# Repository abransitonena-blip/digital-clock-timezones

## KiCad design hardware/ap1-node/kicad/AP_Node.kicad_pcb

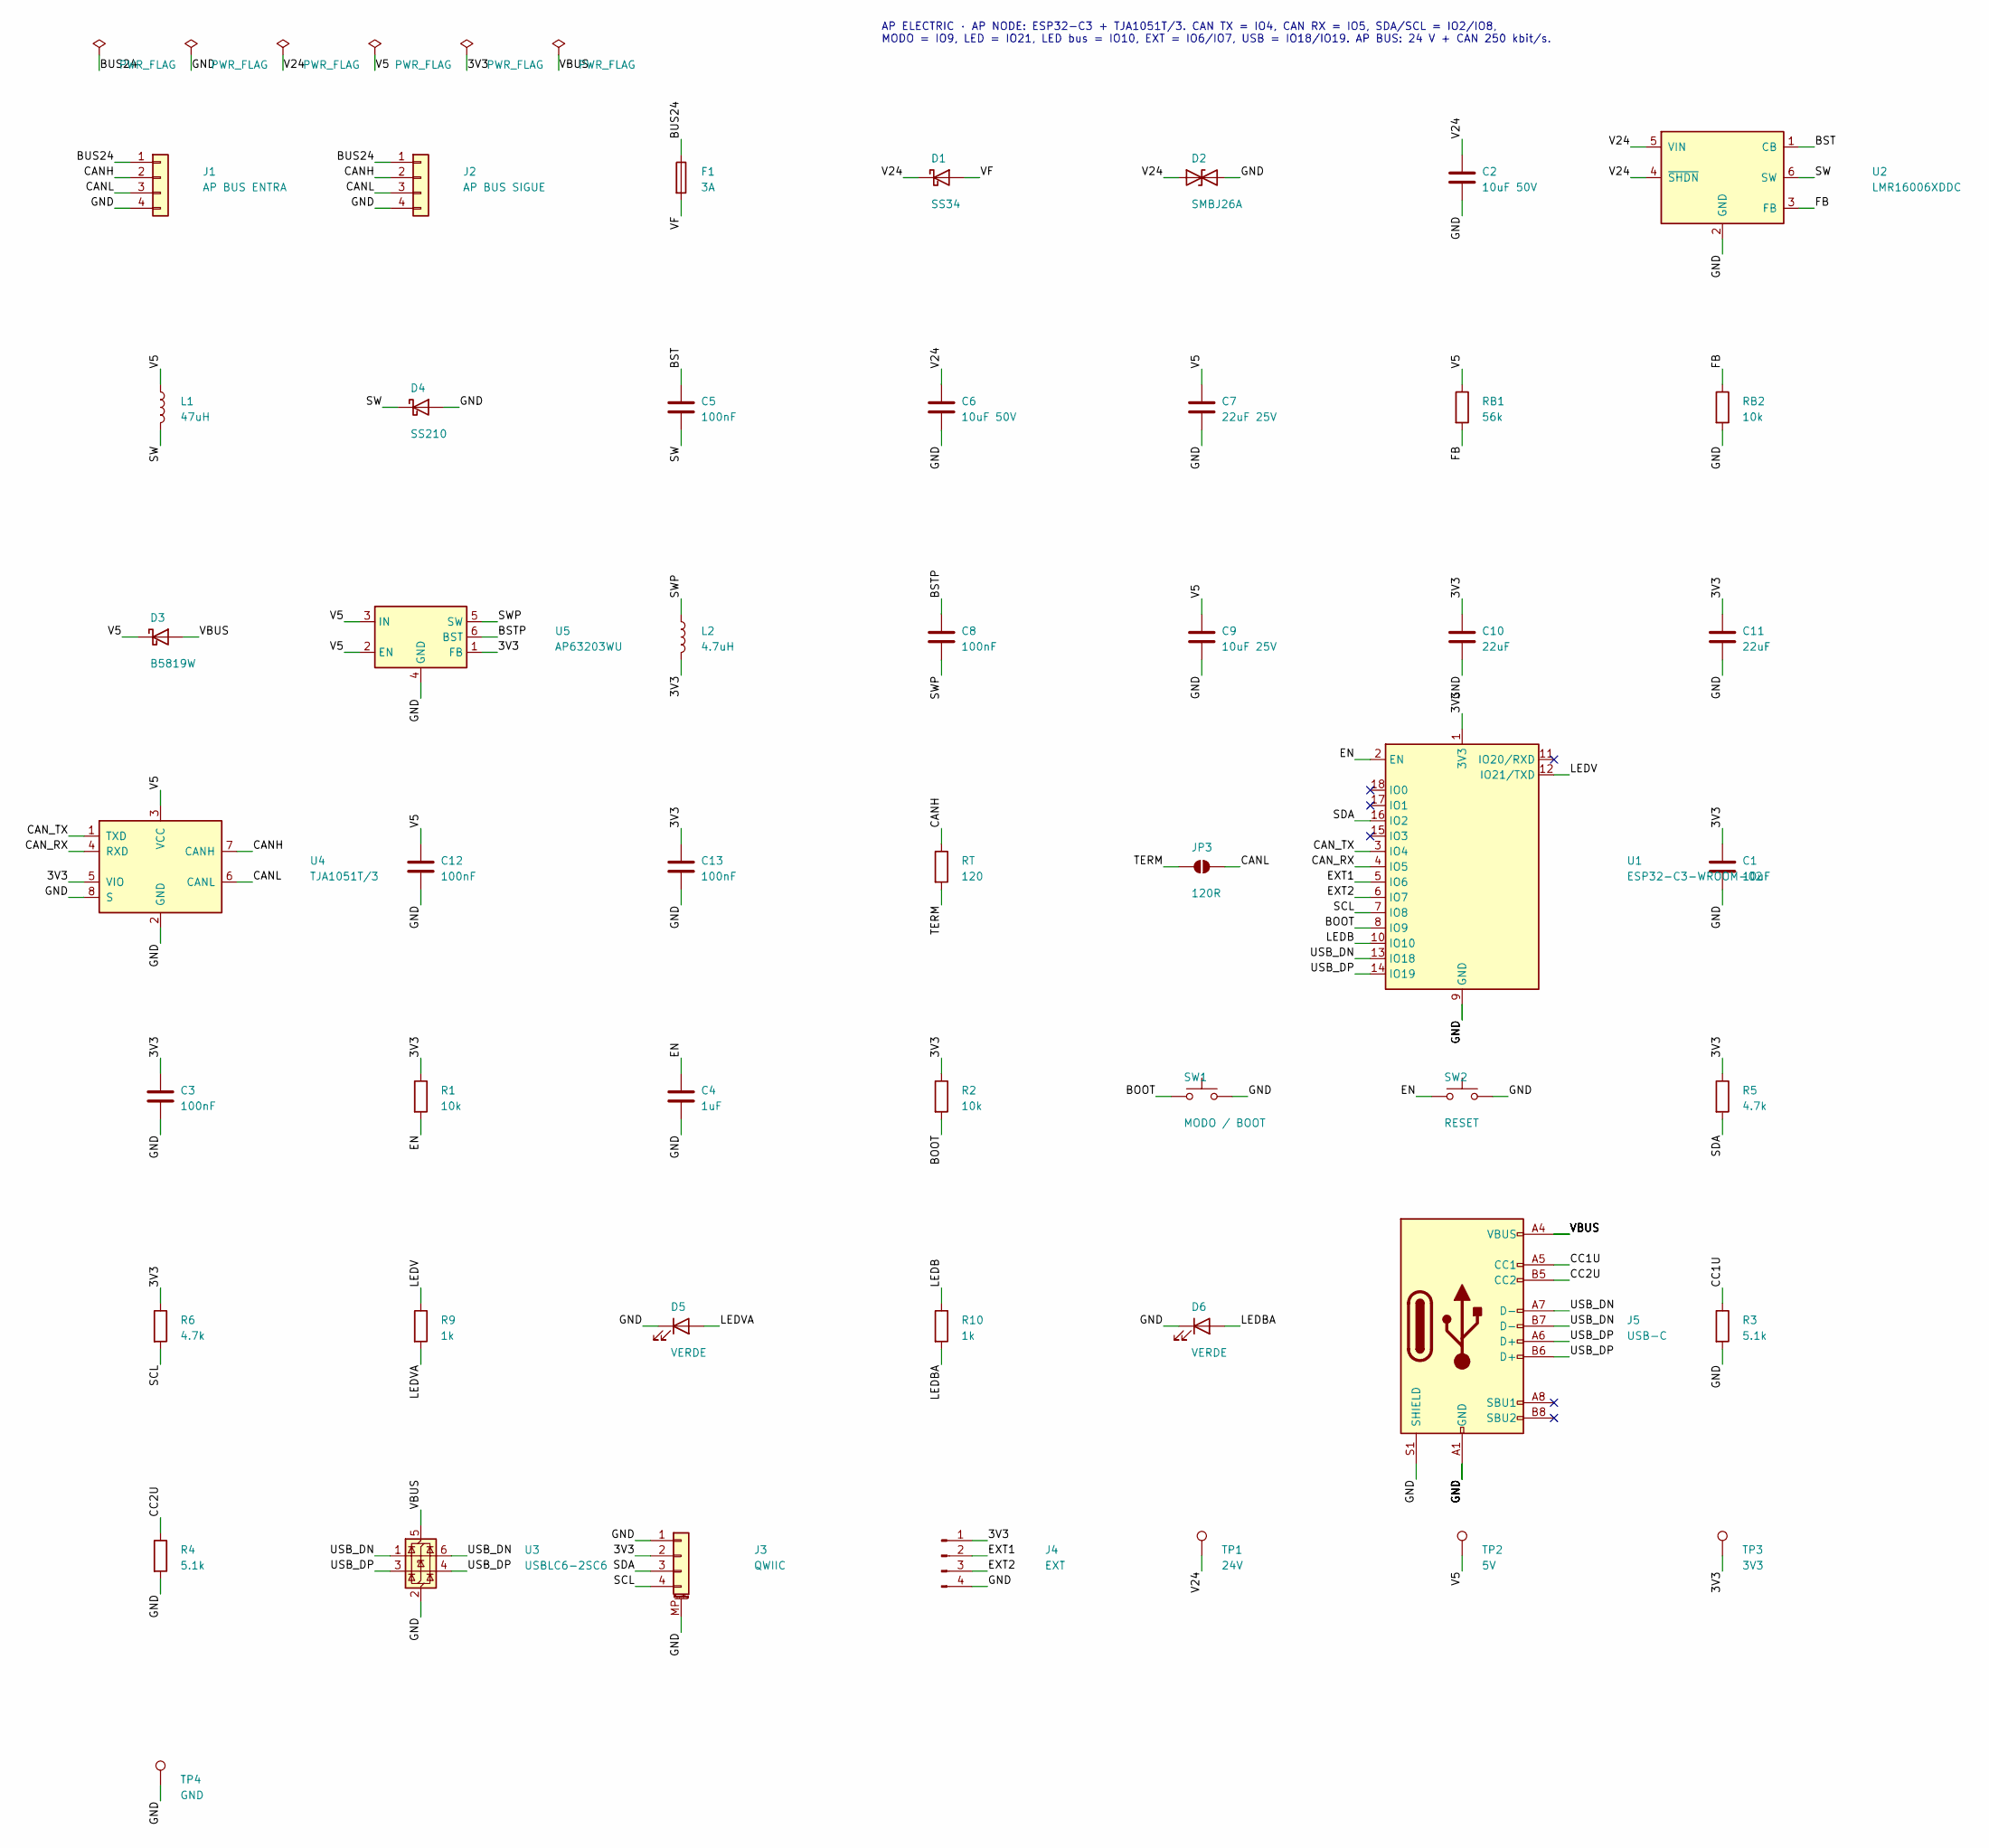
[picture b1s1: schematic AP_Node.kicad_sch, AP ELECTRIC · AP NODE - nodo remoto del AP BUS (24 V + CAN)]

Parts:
C1: 10uF; C_0805_2012Metric
C2, C6: 10uF 50V; C_1206_3216Metric
C3, C5, C8, C12, C13: 100nF; C_0603_1608Metric
C4: 1uF; C_0603_1608Metric
C7: 22uF 25V; C_1206_3216Metric
C9: 10uF 25V; C_1206_3216Metric
C10, C11: 22uF; C_0805_2012Metric
D1: SS34; D_SMA
D2: SMBJ26A; D_SMB
D3: B5819W; D_SOD-123
D4: SS210; D_SMA
D5, D6: VERDE; LED_0603_1608Metric
F1: 3A; Fuse_1206_3216Metric
J1: AP BUS ENTRA; JST_XH_B4B-XH-A_1x04_P2.50mm_Vertical
J2: AP BUS SIGUE; JST_XH_B4B-XH-A_1x04_P2.50mm_Vertical
J3: QWIIC; JST_SH_SM04B-SRSS-TB_1x04-1MP_P1.00mm_Horizontal
J4: EXT; PinHeader_1x04_P2.54mm_Vertical
J5: USB-C; USB_C_Receptacle_HRO_TYPE-C-31-M-12
JP3: 120R; SolderJumper-2_P1.3mm_Open_RoundedPad1.0x1.5mm
L1: 47uH; L_Changjiang_FNR4030S
L2: 4.7uH; L_Changjiang_FNR4030S
R1, R2: 10k; R_0603_1608Metric
R3, R4: 5.1k; R_0603_1608Metric
R5, R6: 4.7k; R_0603_1608Metric
R9, R10: 1k; R_0603_1608Metric
RB1: 56k; R_0603_1608Metric
RB2: 10k; R_0603_1608Metric
RT: 120; R_1206_3216Metric
SW1: MODO / BOOT; SW_Push_1P1T_XKB_TS-1187A
SW2: RESET; SW_Push_1P1T_XKB_TS-1187A
TP1: 24V; TestPoint_Pad_D1.5mm
TP2: 5V; TestPoint_Pad_D1.5mm
TP3: 3V3; TestPoint_Pad_D1.5mm
TP4: GND; TestPoint_Pad_D1.5mm
U1: ESP32-C3-WROOM-02; ESP32-C3-WROOM-02_JLC
U2: LMR16006XDDC; SOT-23-6
U3: USBLC6-2SC6; SOT-23-6
U4: TJA1051T/3; SOIC-8_3.9x4.9mm_P1.27mm
U5: AP63203WU; TSOT-23-6

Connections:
/3V3: C1.1, C3.1, C10.1, C11.1, C13.1, J3.2, J4.1, L2.2, R1.1, R2.1, R5.1, R6.1, TP3.1, U1.1 (3V3), U4.5 (VIO), U5.1 (FB)
/BOOT: R2.2, SW1.1, U1.8 (IO9)
/BST: C5.1, U2.1 (CB)
/BSTP: C8.1, U5.6 (BST)
/BUS24: F1.1, J1.1, J2.1
/CANH: J1.2, J2.2, RT.1, U4.7 (CANH)
/CANL: J1.3, J2.3, JP3.2 (B), U4.6 (CANL)
/CAN_RX: U1.4 (IO5), U4.4 (RXD)
/CAN_TX: U1.3 (IO4), U4.1 (TXD)
/CC1U: J5.A5 (CC1), R3.1
/CC2U: J5.B5 (CC2), R4.1
/EN: C4.1, R1.2, SW2.1, U1.2 (EN)
/EXT1: J4.2, U1.5 (IO6)
/EXT2: J4.3, U1.6 (IO7)
/FB: RB1.2, RB2.1, U2.3 (FB)
/GND: C1.2, C2.2, C3.2, C4.2, C6.2, C7.2, C9.2, C10.2, C11.2, C12.2, C13.2, D2.2 (A2), D4.2 (A), D5.1 (K), D6.1 (K), J1.4, J2.4, J3.1, J3.MP (MountPin), J4.4, J5.A1 (GND), J5.A12 (GND), J5.B1 (GND), J5.B12 (GND), J5.S1 (SHIELD), R3.2, R4.2, RB2.2, SW1.2, SW2.2, TP4.1, U1.9 (GND), U1.19 (GND), U2.2 (GND), U3.2 (GND), U4.2 (GND), U4.8 (S), U5.4 (GND)
/LEDB: R10.1, U1.10 (IO10)
/LEDBA: D6.2 (A), R10.2
/LEDV: R9.1, U1.12 (IO21/TXD)
/LEDVA: D5.2 (A), R9.2
/SCL: J3.4, R6.2, U1.7 (IO8)
/SDA: J3.3, R5.2, U1.16 (IO2)
/SW: C5.2, D4.1 (K), L1.2, U2.6 (SW)
/SWP: C8.2, L2.1, U5.5 (SW)
/TERM: JP3.1 (A), RT.2
/USB_DN: J5.A7 (D-), J5.B7 (D-), U1.13 (IO18), U3.1 (I/O1), U3.6 (I/O1)
/USB_DP: J5.A6 (D+), J5.B6 (D+), U1.14 (IO19), U3.3 (I/O2), U3.4 (I/O2)
/V5: C7.1, C9.1, C12.1, D3.1 (K), L1.1, RB1.1, TP2.1, U4.3 (VCC), U5.2 (EN), U5.3 (IN)
/V24: C2.1, C6.1, D1.1 (K), D2.1 (A1), TP1.1, U2.4 (~SHDN), U2.5 (VIN)
/VBUS: D3.2 (A), J5.A4 (VBUS), J5.A9 (VBUS), J5.B4 (VBUS), J5.B9 (VBUS), U3.5 (VBUS)
/VF: D1.2 (A), F1.2

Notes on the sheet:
AP ELECTRIC · AP NODE: ESP32-C3 + TJA1051T/3. CAN TX = IO4, CAN RX = IO5, SDA/SCL = IO2/IO8, MODO = IO9, LED = IO21, LED bus = IO10, EXT = IO6/IO7, USB = IO18/IO19. AP BUS: 24 V + CAN 250 kbit/s.

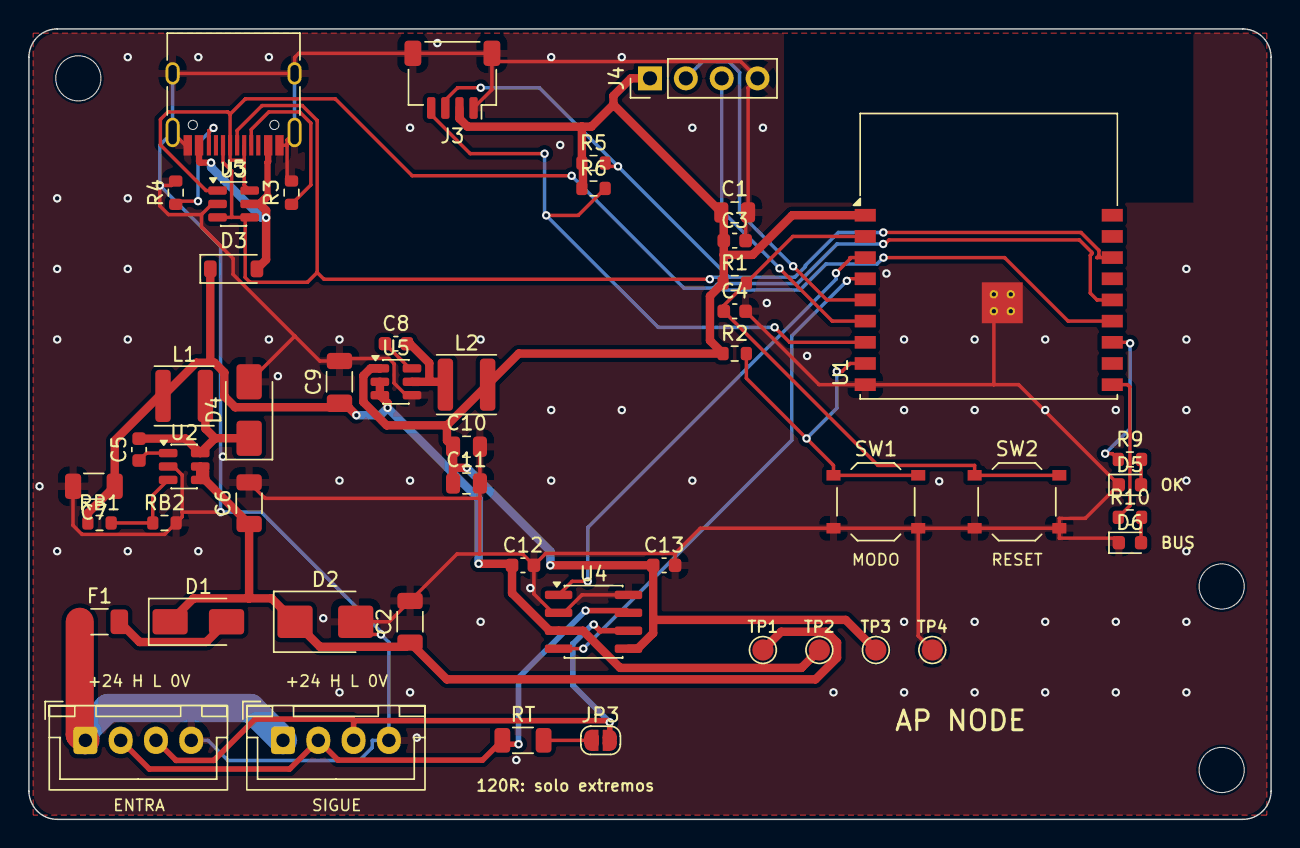
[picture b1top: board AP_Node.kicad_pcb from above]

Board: 2 copper layers, 88.0 x 56.0 mm, 53 parts (0 on the bottom side), 31 nets.

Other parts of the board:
H1, H2, H3: MountingHole_3.2mm_M3

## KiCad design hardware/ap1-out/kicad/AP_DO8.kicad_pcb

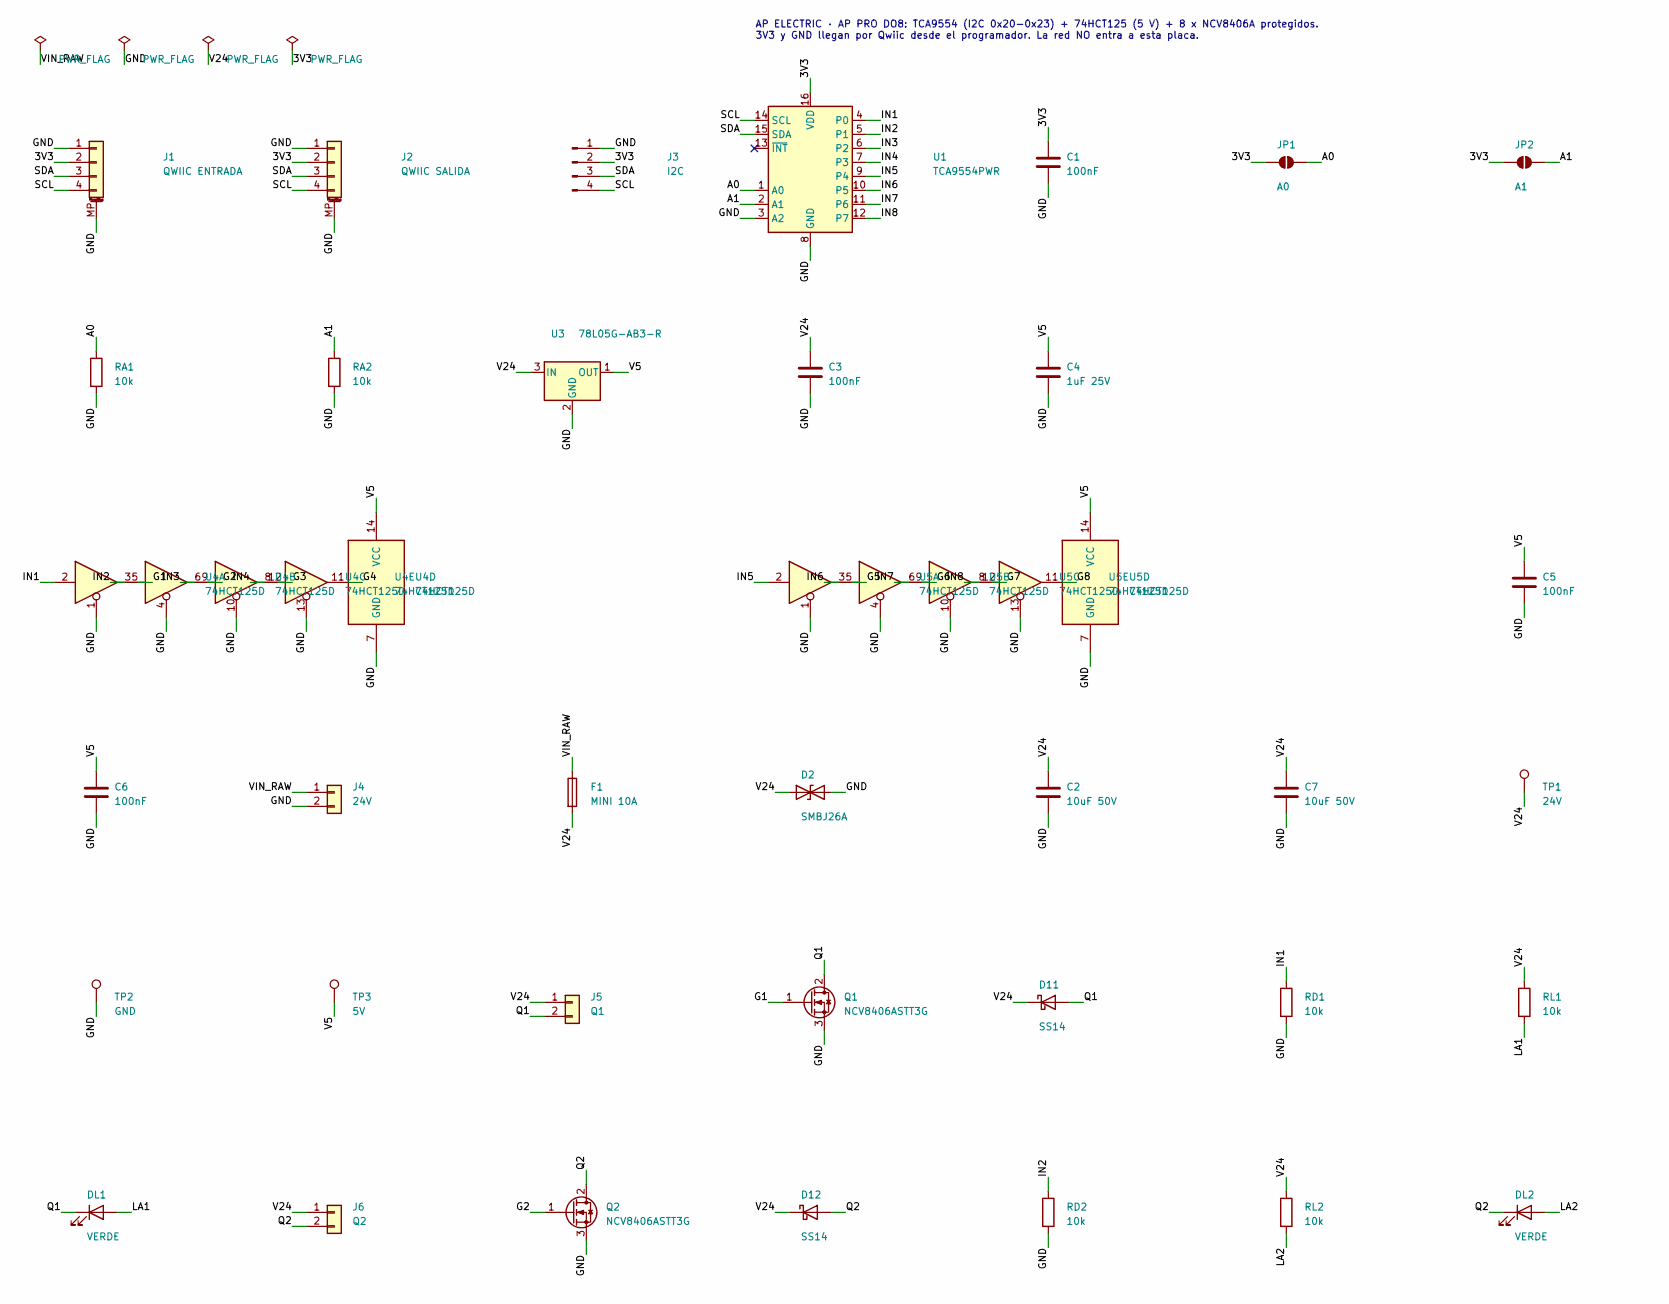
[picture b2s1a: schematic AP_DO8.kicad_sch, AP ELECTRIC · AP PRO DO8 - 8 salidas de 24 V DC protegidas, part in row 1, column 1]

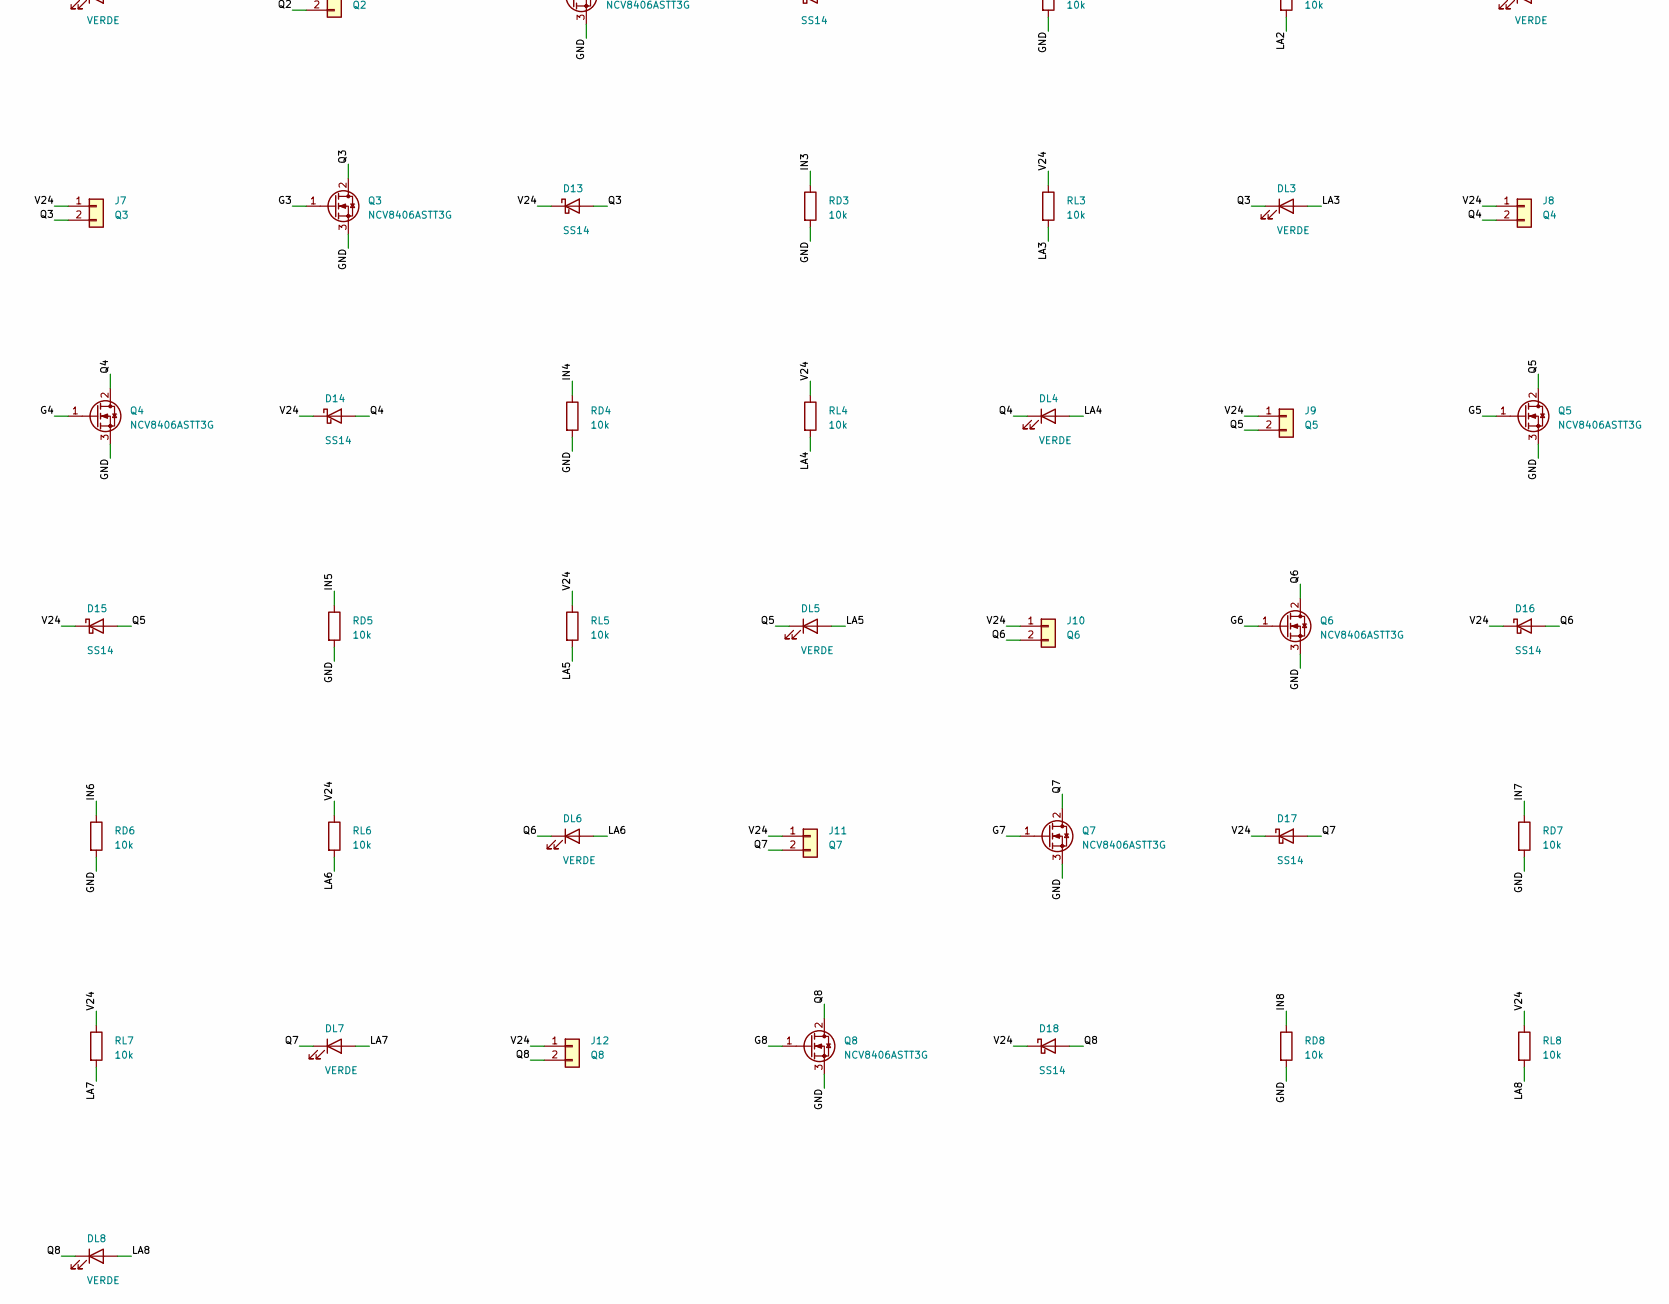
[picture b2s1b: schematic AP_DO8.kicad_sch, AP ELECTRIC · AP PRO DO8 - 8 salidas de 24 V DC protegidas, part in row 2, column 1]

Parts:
C1, C3, C5, C6: 100nF; C_0603_1608Metric
C2, C7: 10uF 50V; C_1206_3216Metric
C4: 1uF 25V; C_0603_1608Metric
D2: SMBJ26A; D_SMB
D11, D12, D13, D14, D15, D16, D17, D18: SS14; D_SMA
DL1, DL2, DL3, DL4, DL5, DL6, DL7, DL8: VERDE; LED_0603_1608Metric
F1: MINI 10A; Fuseholder_Blade_Mini_Keystone_3568
J1: QWIIC ENTRADA; JST_SH_SM04B-SRSS-TB_1x04-1MP_P1.00mm_Horizontal
J2: QWIIC SALIDA; JST_SH_SM04B-SRSS-TB_1x04-1MP_P1.00mm_Horizontal
J3: I2C; PinHeader_1x04_P2.54mm_Vertical
J4: 24V; JST_VH_B2P-VH_1x02_P3.96mm_Vertical
J5: Q1; JST_XH_B2B-XH-A_1x02_P2.50mm_Vertical
J6: Q2; JST_XH_B2B-XH-A_1x02_P2.50mm_Vertical
J7: Q3; JST_XH_B2B-XH-A_1x02_P2.50mm_Vertical
J8: Q4; JST_XH_B2B-XH-A_1x02_P2.50mm_Vertical
J9: Q5; JST_XH_B2B-XH-A_1x02_P2.50mm_Vertical
J10: Q6; JST_XH_B2B-XH-A_1x02_P2.50mm_Vertical
J11: Q7; JST_XH_B2B-XH-A_1x02_P2.50mm_Vertical
J12: Q8; JST_XH_B2B-XH-A_1x02_P2.50mm_Vertical
JP1: A0; SolderJumper-2_P1.3mm_Open_RoundedPad1.0x1.5mm
JP2: A1; SolderJumper-2_P1.3mm_Open_RoundedPad1.0x1.5mm
Q1, Q2, Q3, Q4, Q5, Q6, Q7, Q8: NCV8406ASTT3G; SOT-223-3_TabPin2
RA1, RA2: 10k; R_0603_1608Metric
RD1, RD2, RD3, RD4, RD5, RD6, RD7, RD8: 10k; R_0603_1608Metric
RL1, RL2, RL3, RL4, RL5, RL6, RL7, RL8: 10k; R_0603_1608Metric
TP1: 24V; TestPoint_Pad_D1.5mm
TP2: GND; TestPoint_Pad_D1.5mm
TP3: 5V; TestPoint_Pad_D1.5mm
U1: TCA9554PWR; TSSOP-16_4.4x5mm_P0.65mm
U3: 78L05G-AB3-R; SOT-89-3
U4, U5: 74HCT125D; SOIC-14_3.9x8.7mm_P1.27mm

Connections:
/3V3: C1.1, J1.2, J2.2, J3.2, JP1.1 (A), JP2.1 (A), U1.16 (VDD)
/A0: JP1.2 (B), RA1.1, U1.1 (A0)
/A1: JP2.2 (B), RA2.1, U1.2 (A1)
/G1: Q1.1 (G), U4.3
/G2: Q2.1 (G), U4.6
/G3: Q3.1 (G), U4.8
/G4: Q4.1 (G), U4.11
/G5: Q5.1 (G), U5.3
/G6: Q6.1 (G), U5.6
/G7: Q7.1 (G), U5.8
/G8: Q8.1 (G), U5.11
/GND: C1.2, C2.2, C3.2, C4.2, C5.2, C6.2, C7.2, D2.2 (A2), J1.1, J1.MP (MountPin), J2.1, J2.MP (MountPin), J3.1, J4.2, Q1.3 (S), Q2.3 (S), Q3.3 (S), Q4.3 (S), Q5.3 (S), Q6.3 (S), Q7.3 (S), Q8.3 (S), RA1.2, RA2.2, RD1.2, RD2.2, RD3.2, RD4.2, RD5.2, RD6.2, RD7.2, RD8.2, TP2.1, U1.3 (A2), U1.8 (GND), U3.2 (GND), U4.1, U4.4, U4.7 (GND), U4.10, U4.13, U5.1, U5.4, U5.7 (GND), U5.10, U5.13
/IN1: RD1.1, U1.4 (P0), U4.2
/IN2: RD2.1, U1.5 (P1), U4.5
/IN3: RD3.1, U1.6 (P2), U4.9
/IN4: RD4.1, U1.7 (P3), U4.12
/IN5: RD5.1, U1.9 (P4), U5.2
/IN6: RD6.1, U1.10 (P5), U5.5
/IN7: RD7.1, U1.11 (P6), U5.9
/IN8: RD8.1, U1.12 (P7), U5.12
/LA1: DL1.2 (A), RL1.2
/LA2: DL2.2 (A), RL2.2
/LA3: DL3.2 (A), RL3.2
/LA4: DL4.2 (A), RL4.2
/LA5: DL5.2 (A), RL5.2
/LA6: DL6.2 (A), RL6.2
/LA7: DL7.2 (A), RL7.2
/LA8: DL8.2 (A), RL8.2
/Q1: D11.2 (A), DL1.1 (K), J5.2, Q1.2 (D)
/Q2: D12.2 (A), DL2.1 (K), J6.2, Q2.2 (D)
/Q3: D13.2 (A), DL3.1 (K), J7.2, Q3.2 (D)
/Q4: D14.2 (A), DL4.1 (K), J8.2, Q4.2 (D)
/Q5: D15.2 (A), DL5.1 (K), J9.2, Q5.2 (D)
/Q6: D16.2 (A), DL6.1 (K), J10.2, Q6.2 (D)
/Q7: D17.2 (A), DL7.1 (K), J11.2, Q7.2 (D)
/Q8: D18.2 (A), DL8.1 (K), J12.2, Q8.2 (D)
/SCL: J1.4, J2.4, J3.4, U1.14 (SCL)
/SDA: J1.3, J2.3, J3.3, U1.15 (SDA)
/V5: C4.1, C5.1, C6.1, TP3.1, U3.1 (OUT), U4.14 (VCC), U5.14 (VCC)
/V24: C2.1, C3.1, C7.1, D2.1 (A1), D11.1 (K), D12.1 (K), D13.1 (K), D14.1 (K), D15.1 (K), D16.1 (K), D17.1 (K), D18.1 (K), F1.2, J5.1, J6.1, J7.1, J8.1, J9.1, J10.1, J11.1, J12.1, RL1.1, RL2.1, RL3.1, RL4.1, RL5.1, RL6.1, RL7.1, RL8.1, TP1.1, U3.3 (IN)
/VIN_RAW: F1.1, J4.1

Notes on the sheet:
AP ELECTRIC · AP PRO DO8: TCA9554 (I2C 0x20-0x23) + 74HCT125 (5 V) + 8 x NCV8406A protegidos. 3V3 y GND llegan por Qwiic desde el programador. La red NO entra a esta placa.

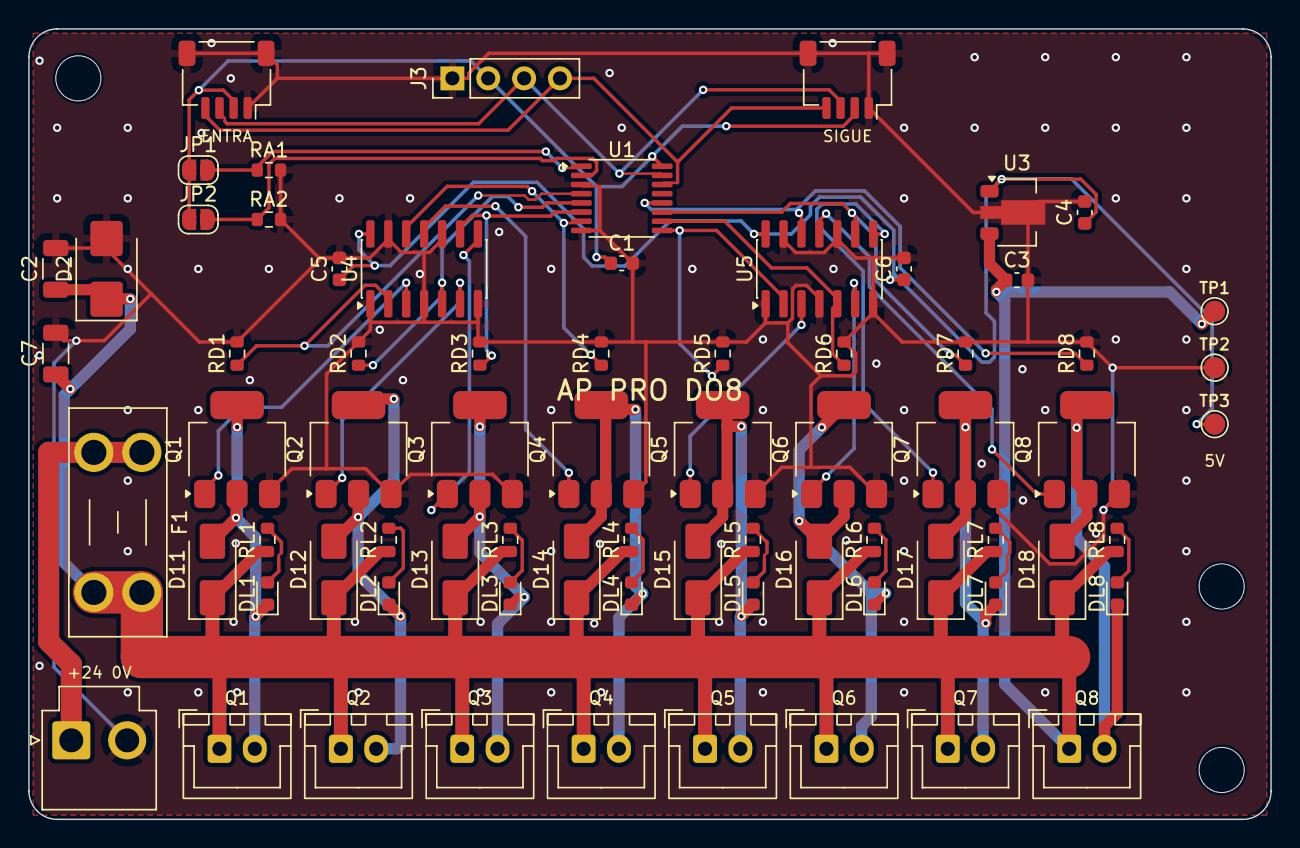
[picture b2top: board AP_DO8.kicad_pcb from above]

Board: 2 copper layers, 88.0 x 56.0 mm, 75 parts (0 on the bottom side), 41 nets.

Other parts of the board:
H1, H2, H3: MountingHole_3.2mm_M3

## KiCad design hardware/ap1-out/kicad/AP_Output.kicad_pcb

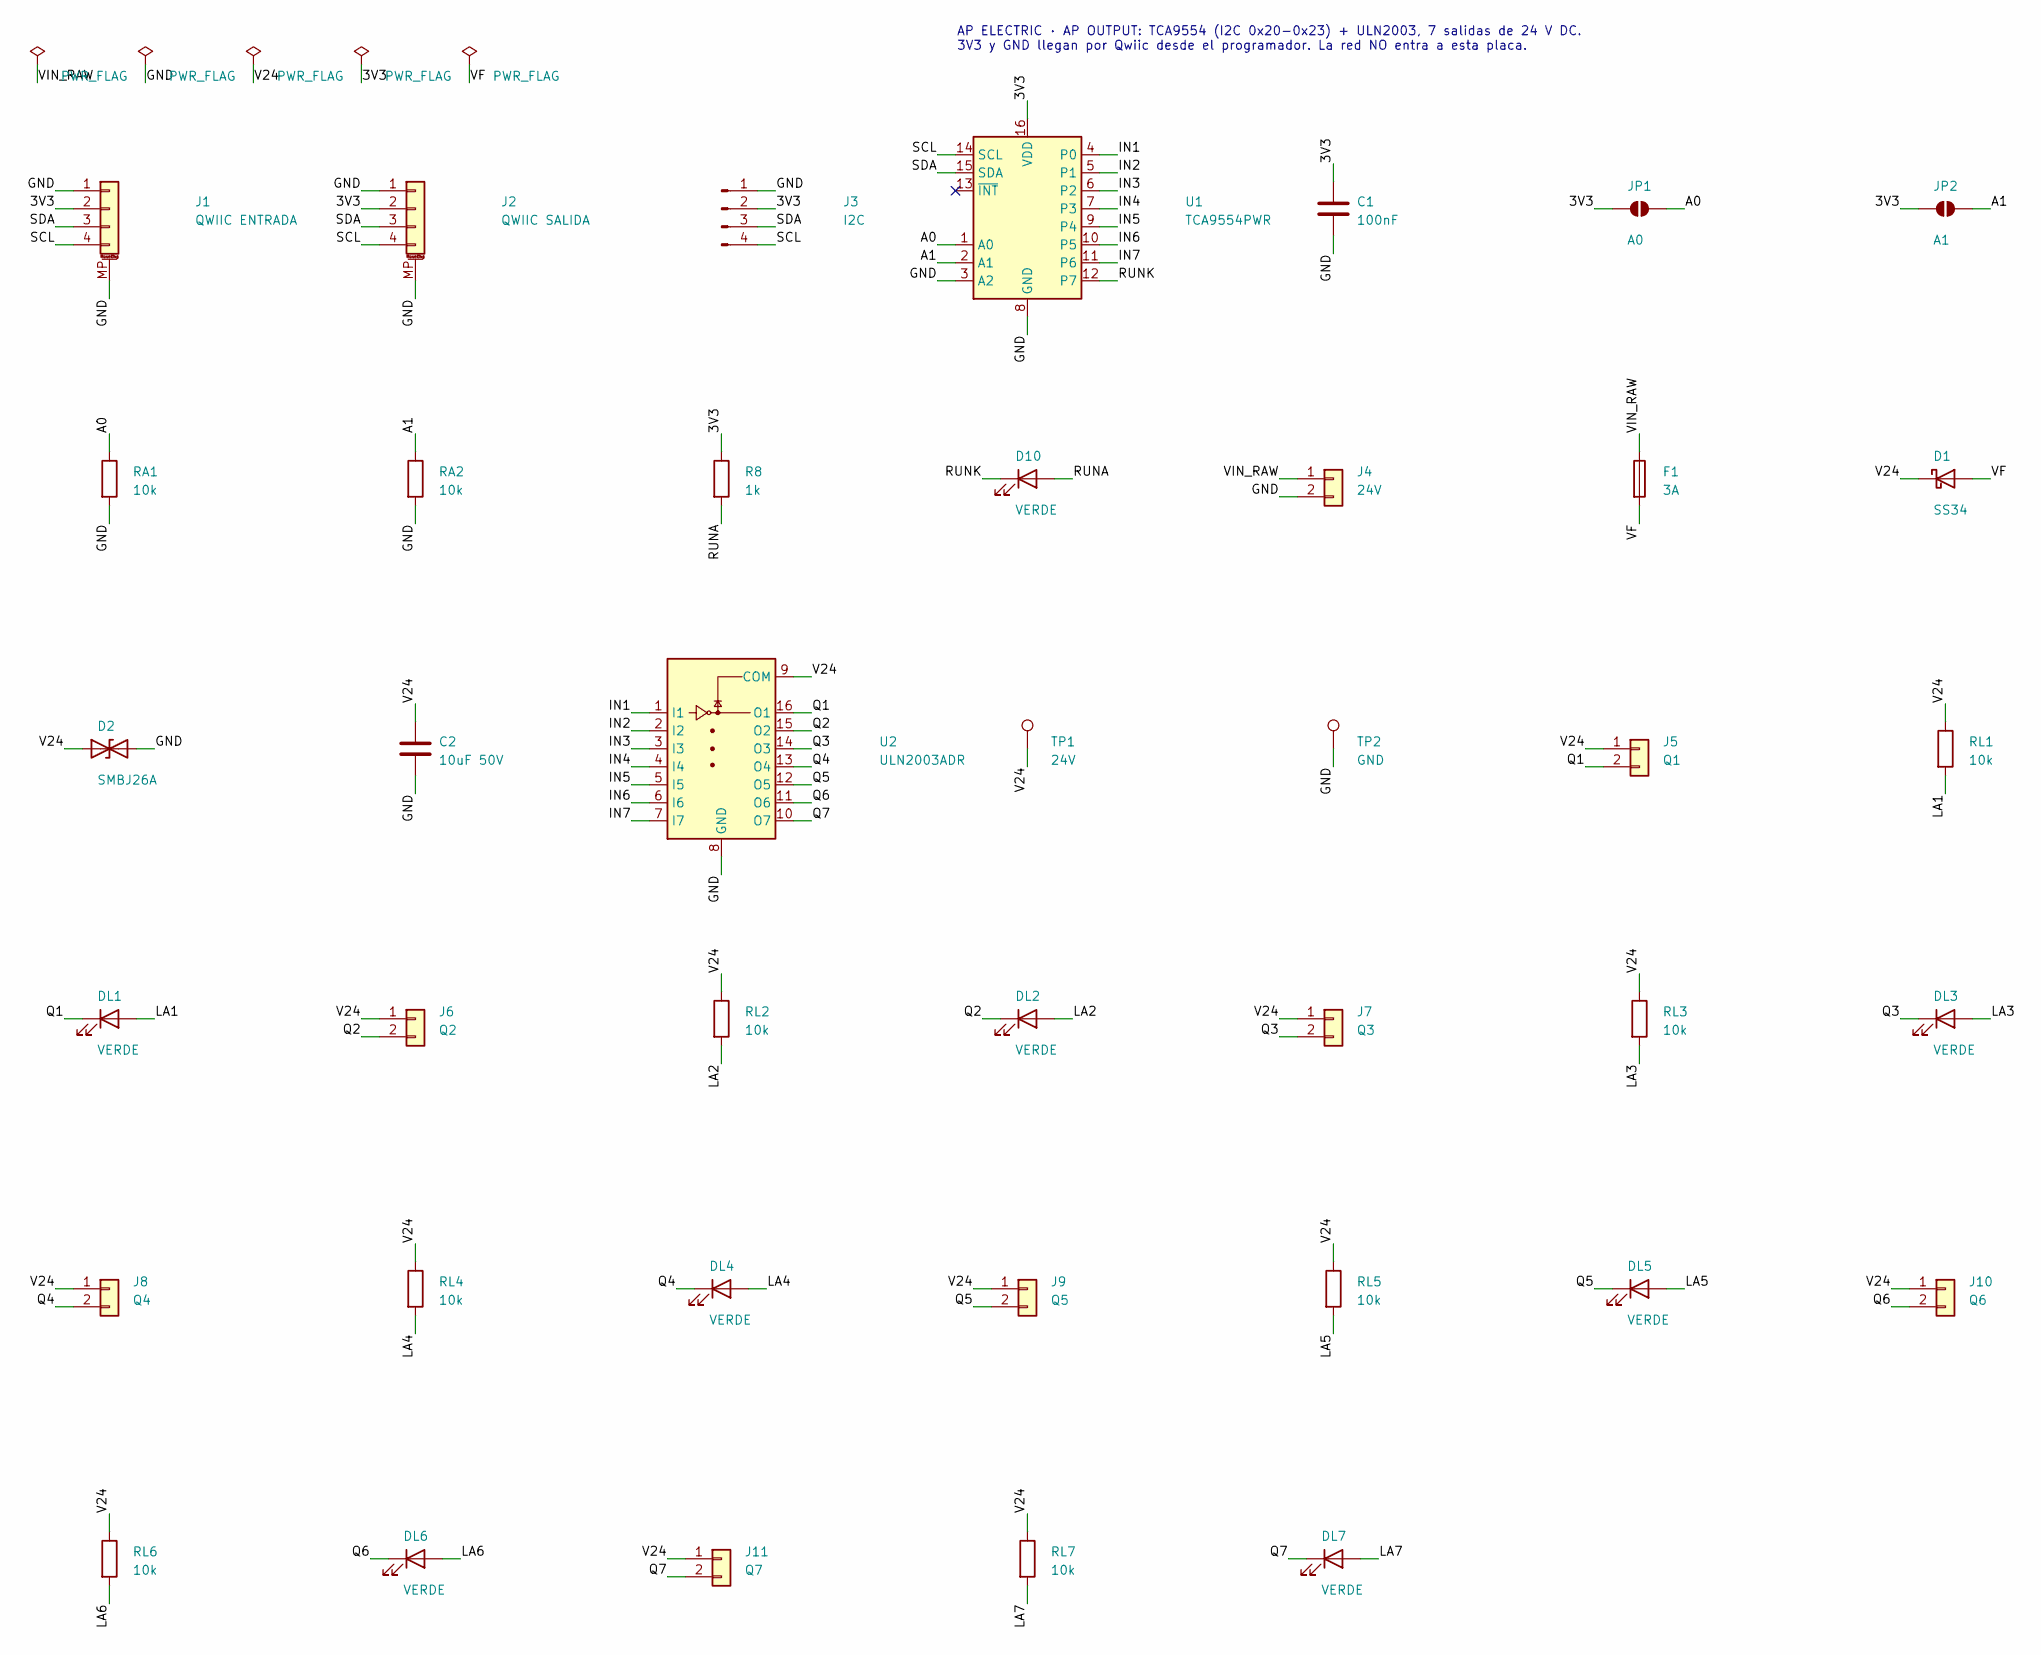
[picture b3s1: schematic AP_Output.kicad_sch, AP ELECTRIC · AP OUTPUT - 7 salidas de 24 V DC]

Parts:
C1: 100nF; C_0603_1608Metric
C2: 10uF 50V; C_1206_3216Metric
D1: SS34; D_SMA
D2: SMBJ26A; D_SMB
D10: VERDE; LED_0603_1608Metric
DL1, DL2, DL3, DL4, DL5, DL6, DL7: VERDE; LED_0603_1608Metric
F1: 3A; Fuse_1206_3216Metric
J1: QWIIC ENTRADA; JST_SH_SM04B-SRSS-TB_1x04-1MP_P1.00mm_Horizontal
J2: QWIIC SALIDA; JST_SH_SM04B-SRSS-TB_1x04-1MP_P1.00mm_Horizontal
J3: I2C; PinHeader_1x04_P2.54mm_Vertical
J4: 24V; JST_VH_B2P-VH_1x02_P3.96mm_Vertical
J5: Q1; JST_XH_B2B-XH-A_1x02_P2.50mm_Vertical
J6: Q2; JST_XH_B2B-XH-A_1x02_P2.50mm_Vertical
J7: Q3; JST_XH_B2B-XH-A_1x02_P2.50mm_Vertical
J8: Q4; JST_XH_B2B-XH-A_1x02_P2.50mm_Vertical
J9: Q5; JST_XH_B2B-XH-A_1x02_P2.50mm_Vertical
J10: Q6; JST_XH_B2B-XH-A_1x02_P2.50mm_Vertical
J11: Q7; JST_XH_B2B-XH-A_1x02_P2.50mm_Vertical
JP1: A0; SolderJumper-2_P1.3mm_Open_RoundedPad1.0x1.5mm
JP2: A1; SolderJumper-2_P1.3mm_Open_RoundedPad1.0x1.5mm
R8: 1k; R_0603_1608Metric
RA1, RA2: 10k; R_0603_1608Metric
RL1, RL2, RL3, RL4, RL5, RL6, RL7: 10k; R_0603_1608Metric
TP1: 24V; TestPoint_Pad_D1.5mm
TP2: GND; TestPoint_Pad_D1.5mm
U1: TCA9554PWR; TSSOP-16_4.4x5mm_P0.65mm
U2: ULN2003ADR; SOIC-16_3.9x9.9mm_P1.27mm

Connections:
/3V3: C1.1, J1.2, J2.2, J3.2, JP1.1 (A), JP2.1 (A), R8.1, U1.16 (VDD)
/A0: JP1.2 (B), RA1.1, U1.1 (A0)
/A1: JP2.2 (B), RA2.1, U1.2 (A1)
/GND: C1.2, C2.2, D2.2 (A2), J1.1, J1.MP (MountPin), J2.1, J2.MP (MountPin), J3.1, J4.2, RA1.2, RA2.2, TP2.1, U1.3 (A2), U1.8 (GND), U2.8 (GND)
/IN1: U1.4 (P0), U2.1 (I1)
/IN2: U1.5 (P1), U2.2 (I2)
/IN3: U1.6 (P2), U2.3 (I3)
/IN4: U1.7 (P3), U2.4 (I4)
/IN5: U1.9 (P4), U2.5 (I5)
/IN6: U1.10 (P5), U2.6 (I6)
/IN7: U1.11 (P6), U2.7 (I7)
/LA1: DL1.2 (A), RL1.2
/LA2: DL2.2 (A), RL2.2
/LA3: DL3.2 (A), RL3.2
/LA4: DL4.2 (A), RL4.2
/LA5: DL5.2 (A), RL5.2
/LA6: DL6.2 (A), RL6.2
/LA7: DL7.2 (A), RL7.2
/Q1: DL1.1 (K), J5.2, U2.16 (O1)
/Q2: DL2.1 (K), J6.2, U2.15 (O2)
/Q3: DL3.1 (K), J7.2, U2.14 (O3)
/Q4: DL4.1 (K), J8.2, U2.13 (O4)
/Q5: DL5.1 (K), J9.2, U2.12 (O5)
/Q6: DL6.1 (K), J10.2, U2.11 (O6)
/Q7: DL7.1 (K), J11.2, U2.10 (O7)
/RUNA: D10.2 (A), R8.2
/RUNK: D10.1 (K), U1.12 (P7)
/SCL: J1.4, J2.4, J3.4, U1.14 (SCL)
/SDA: J1.3, J2.3, J3.3, U1.15 (SDA)
/V24: C2.1, D1.1 (K), D2.1 (A1), J5.1, J6.1, J7.1, J8.1, J9.1, J10.1, J11.1, RL1.1, RL2.1, RL3.1, RL4.1, RL5.1, RL6.1, RL7.1, TP1.1, U2.9 (COM)
/VF: D1.2 (A), F1.2
/VIN_RAW: F1.1, J4.1

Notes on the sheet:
AP ELECTRIC · AP OUTPUT: TCA9554 (I2C 0x20-0x23) + ULN2003, 7 salidas de 24 V DC. 3V3 y GND llegan por Qwiic desde el programador. La red NO entra a esta placa.

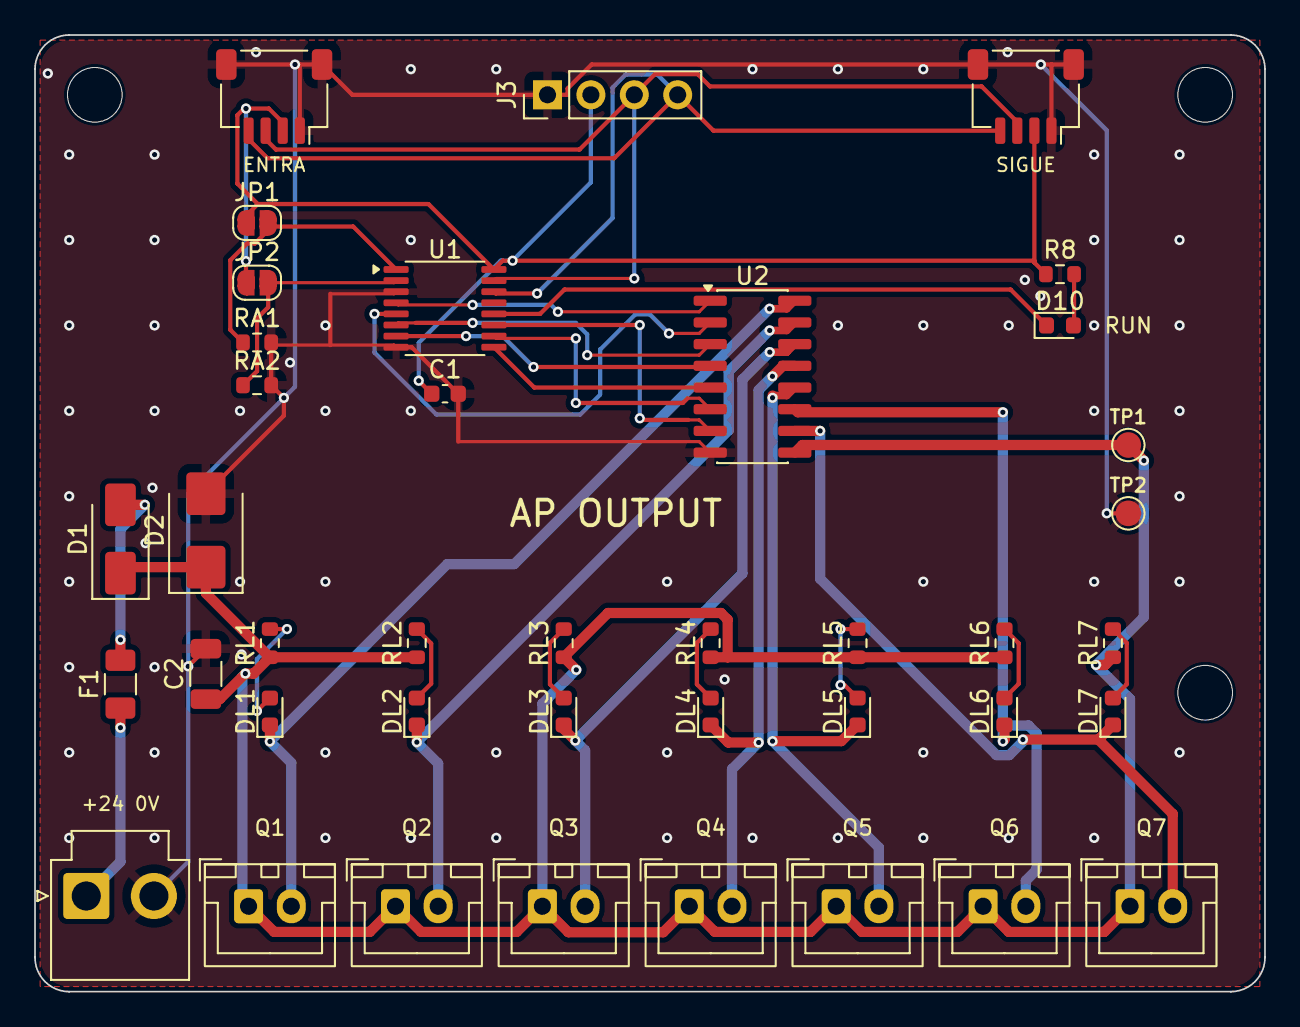
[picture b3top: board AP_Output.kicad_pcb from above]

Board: 2 copper layers, 72.0 x 56.0 mm, 43 parts (0 on the bottom side), 32 nets.

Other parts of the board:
H1, H2, H3: MountingHole_3.2mm_M3
